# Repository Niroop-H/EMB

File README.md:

# EMB native KiCad automation

See [desktop automation setup, verification policy and Windows packaging](kicad_ai/AUTOMATION.md).
The automation companion preserves the original KiCad editors and engines.
Legacy generated certificates are not manufacturing approvals.

# KiCad README

For specific documentation about [building KiCad](https://dev-docs.kicad.org/en/build/), policies
and guidelines, and source code documentation see the
[Developer Documentation](https://dev-docs.kicad.org) website.

You may also take a look into the [Wiki](https://gitlab.com/kicad/code/kicad/-/wikis/home),
the [contribution guide](https://dev-docs.kicad.org/en/contribute/).

For general information about KiCad and information about contributing to the documentation and
libraries, see our [Website](https://kicad.org/) and our [Forum](https://forum.kicad.info/).

## Build state

KiCad uses a host of CI resources.

GitLab CI pipeline status can be viewed for Linux and Windows builds of the latest commits.

## Release status

## Files
* [AUTHORS.txt](AUTHORS.txt) - The authors, contributors, document writers and translators list
* [CMakeLists.txt](CMakeLists.txt) - Main CMAKE build tool script
* [copyright.h](copyright.h) - A very short copy of the GNU General Public License to be included in new source files
* [Doxyfile](Doxyfile) - Doxygen config file for KiCad
* [INSTALL.txt](INSTALL.txt) - The release (binary) installation instructions
* [uncrustify.cfg](uncrustify.cfg) - Uncrustify config file for uncrustify sources formatting tool
* [_clang-format](_clang-format) - clang config file for clang-format sources formatting tool

## Subdirectories

* [3d-viewer](3d-viewer)         - Sourcecode of the 3D viewer
* [cmake](cmake)      - Modules for the CMAKE build tool
* [common](common)            - Sourcecode of the common library
* [cvpcb](cvpcb)             - Sourcecode of the CvPCB tool
* [demos](demos)             - Some demo examples
* [doxygen](doxygen)     - Configuration for generating pretty doxygen manual of the codebase
* [eeschema](eeschema)          - Sourcecode of the schematic editor
* [gerbview](gerbview)          - Sourcecode of the gerber viewer
* [include](include)           - Interfaces to the common library
* [kicad](kicad)             - Sourcecode of the project manager
* [libs](libs)           - Sourcecode of KiCad utilities (geometry and others)
* [pagelayout_editor](pagelayout_editor) - Sourcecode of the pagelayout editor
* [patches](patches)           - Collection of patches for external dependencies
* [pcbnew](pcbnew)           - Sourcecode of the printed circuit board editor
* [plugins](plugins)           - Sourcecode for the 3D viewer plugins
* [qa](qa)                - Unit testing framework for KiCad
* [resources](resources)         - Packaging resources such as bitmaps and operating system specific files
    - [bitmaps_png](resources/bitmaps_png)       - Menu and program icons
    - [project_template](resources/project_template)          - Project template
* [thirdparty](thirdparty)           - Sourcecode of external libraries used in KiCad but not written by the KiCad team
* [tools](tools)             - Helpers for developing, testing and building
* [translation](translation) - Translation data files (managed through [Weblate](https://hosted.weblate.org/projects/kicad/master-source/) for most languages)
* [utils](utils)             - Small utils for KiCad, e.g. IDF, STEP, and OGL tools and converters

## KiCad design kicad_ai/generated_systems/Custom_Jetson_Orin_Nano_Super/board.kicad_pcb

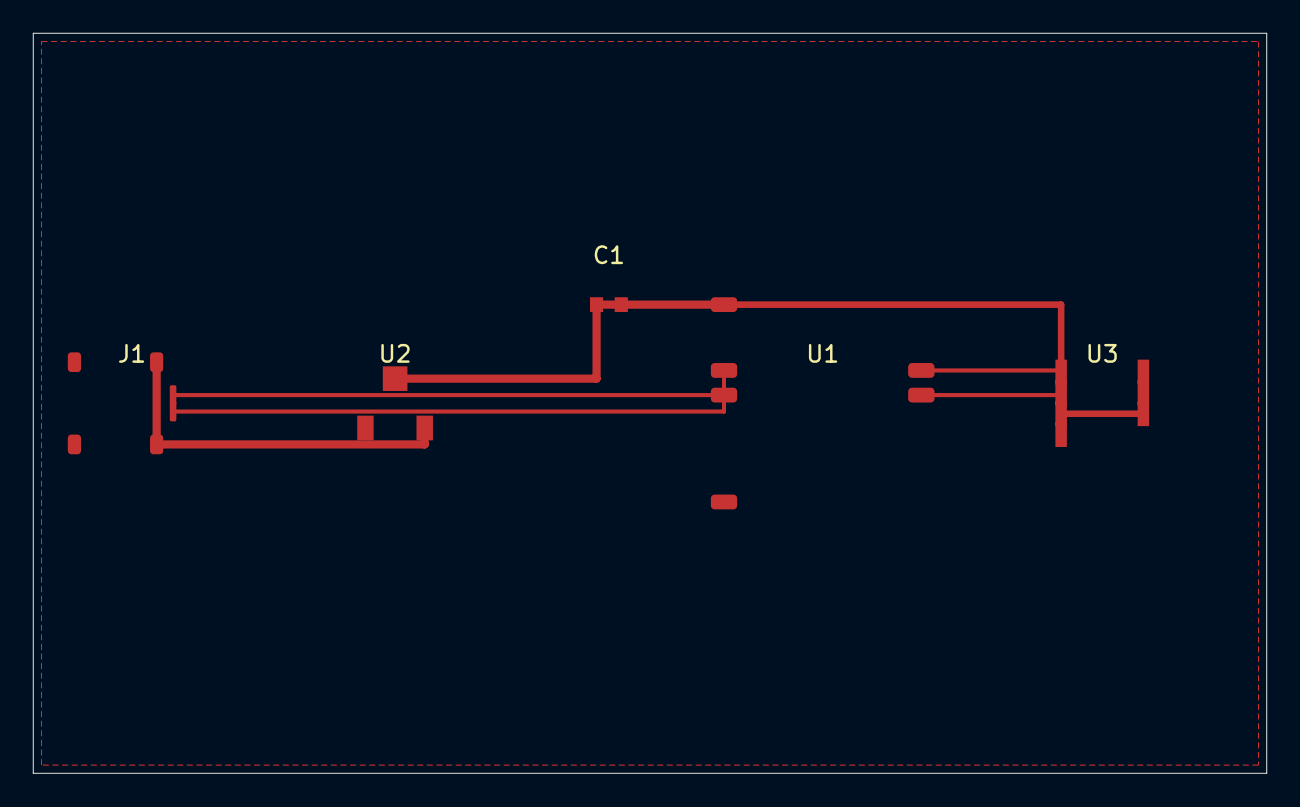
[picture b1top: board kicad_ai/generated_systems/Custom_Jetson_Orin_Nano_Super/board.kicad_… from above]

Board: 2 copper layers, 75.0 x 45.0 mm, 5 parts (0 on the bottom side), 7 nets.

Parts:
C1: 100nF; C_0603_1608Metric
J1: USB-C; USB_C_Receptacle_HRO_TYPE-C-31-M-12
U1: ESP32-S3; ESP32-S3-WROOM-1
U2: AMS1117-3.3; SOT-223-3_TabPin2
U3: SN65HVD230DR; SOIC-8_3.9x4.9mm_P1.27mm

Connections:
+3V3: C1.1, U1.2, U2.2, U3.3, U3.8
CAN_RX: U1.5, U3.4
CAN_TX: U1.4, U3.1
GND: C1.2, J1.A1, J1.B1, U1.1, U2.1, U3.2
USB_DN: J1.A7, U1.20
USB_DP: J1.A6, U1.19
VBUS: J1.A4, J1.B4, U2.3

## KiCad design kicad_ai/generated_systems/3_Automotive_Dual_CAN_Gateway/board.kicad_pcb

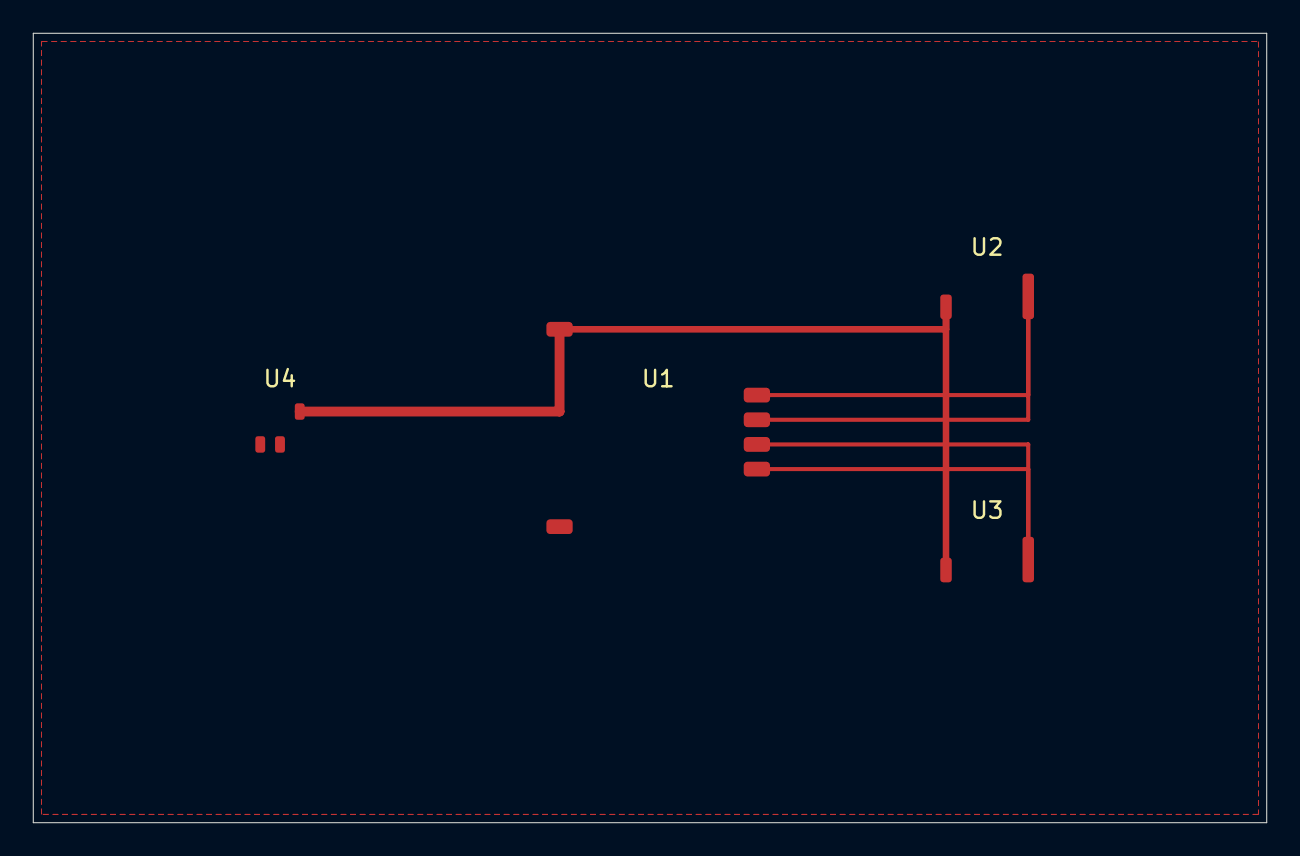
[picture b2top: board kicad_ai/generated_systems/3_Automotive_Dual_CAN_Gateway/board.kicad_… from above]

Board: 2 copper layers, 75.0 x 48.0 mm, 4 parts (0 on the bottom side), 6 nets.

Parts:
U1: ESP32-S3; ESP32-S3-WROOM-1
U2: CAN1; SOIC-8_3.9x4.9mm_P1.27mm
U3: CAN2; SOIC-8_3.9x4.9mm_P1.27mm
U4: TPS54302; SOT-23-6

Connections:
+3V3: U1.2, U2.3, U3.3, U4.6
CAN1_H: U1.4, U2.7
CAN1_L: U1.5, U2.6
CAN2_H: U1.6, U3.7
CAN2_L: U1.7, U3.6
GND: U1.1, U4.2

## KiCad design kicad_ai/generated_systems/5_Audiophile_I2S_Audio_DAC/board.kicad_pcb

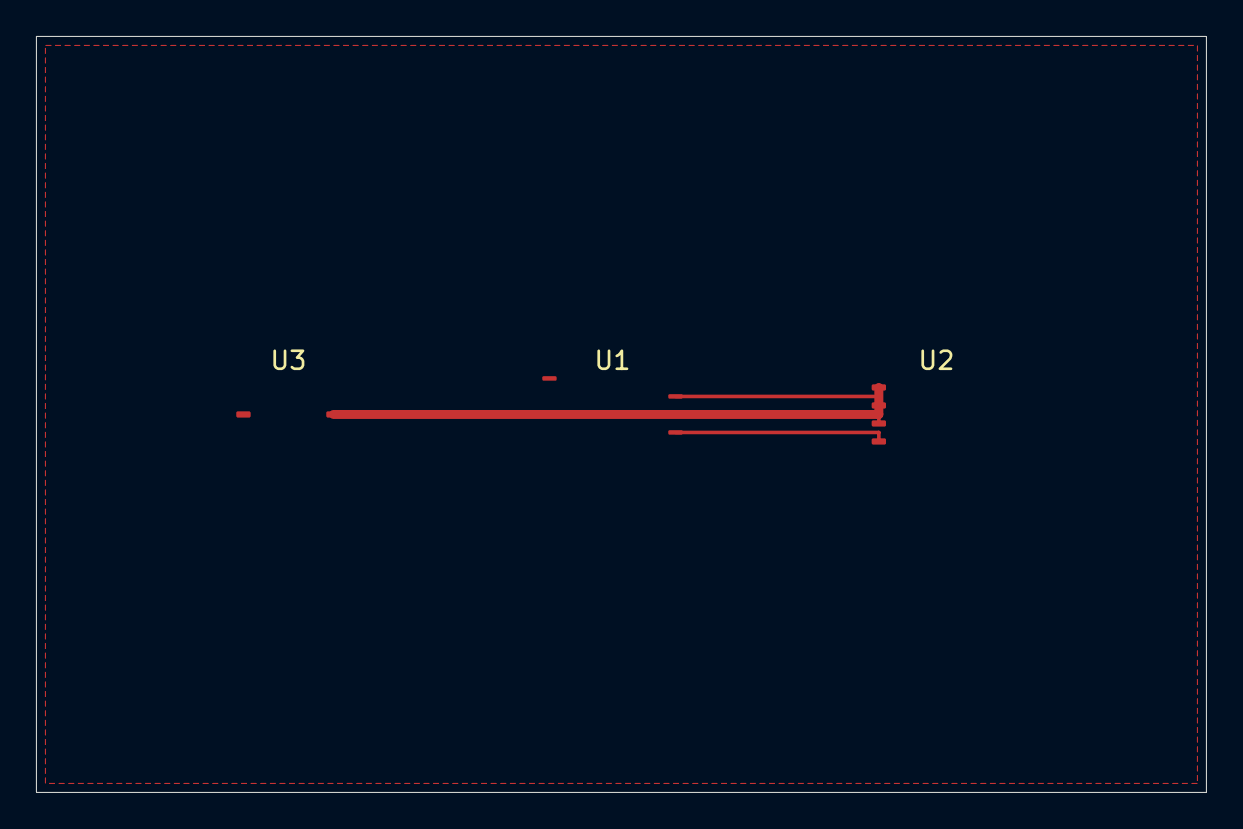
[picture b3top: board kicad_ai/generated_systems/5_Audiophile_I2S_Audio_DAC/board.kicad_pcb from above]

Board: 2 copper layers, 65.0 x 42.0 mm, 3 parts (0 on the bottom side), 4 nets.

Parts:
U1: RP2040; QFN-56-1EP_7x7mm_P0.4mm_EP3.2x3.2mm
U2: PCM5102A; TSSOP-20_4.4x6.5mm_P0.65mm
U3: TPS7A47; QFN-20-1EP_5x5mm_P0.65mm_EP3.1x3.1mm

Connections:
+3V3_ANA: U2.1, U3.5
I2S_BCLK: U1.15, U2.12
I2S_DATA: U1.17, U2.14
I2S_LRCK: U1.16, U2.13

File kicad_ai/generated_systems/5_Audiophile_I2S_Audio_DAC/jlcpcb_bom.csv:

Comment,Designator,Footprint,LCSC Part #
RP2040,U1,Package_DFN_QFN:QFN-56-1EP_7x7mm_P0.4mm_EP3.2x3.2mm,TBD
PCM5102APWR,U2,Package_SO:TSSOP-20_4.4x6.5mm_P0.65mm,TBD
TPS7A4700RGWR,U3,Package_DFN_QFN:QFN-20-1EP_5x5mm_P0.65mm_EP3.1x3.1mm,TBD

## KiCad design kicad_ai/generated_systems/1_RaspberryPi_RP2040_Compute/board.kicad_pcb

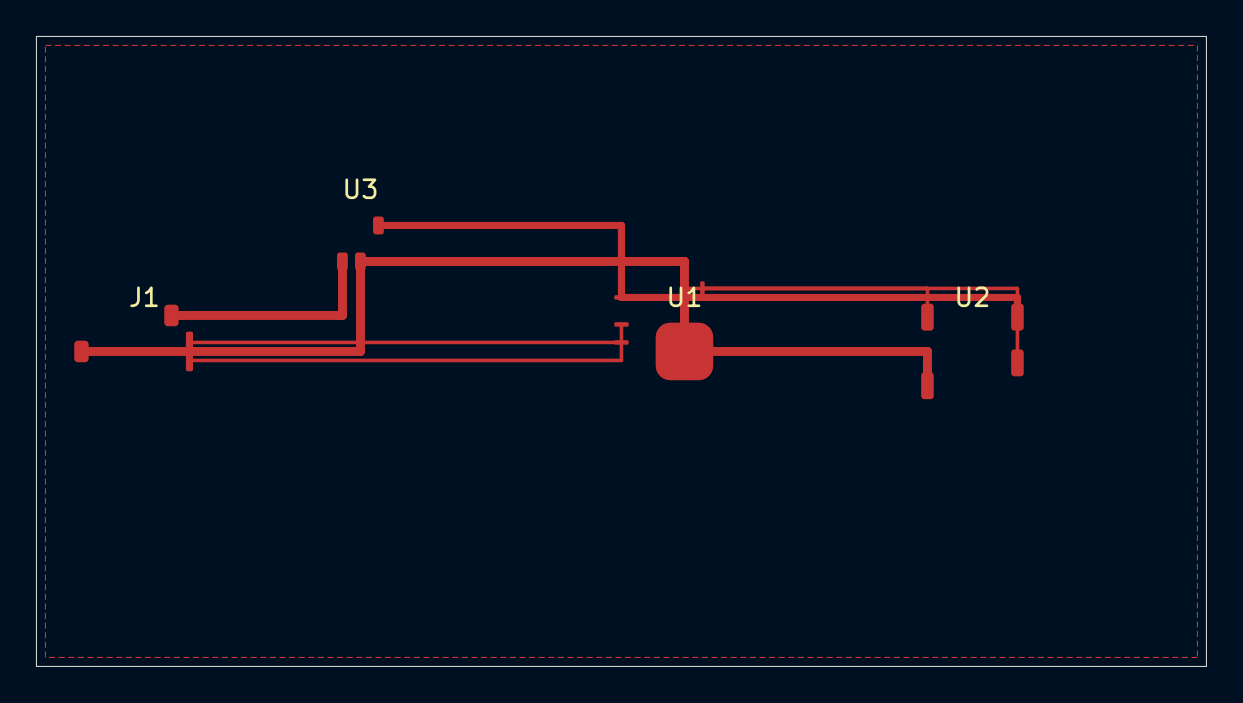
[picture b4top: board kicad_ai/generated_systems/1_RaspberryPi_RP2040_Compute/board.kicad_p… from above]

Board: 2 copper layers, 65.0 x 35.0 mm, 4 parts (0 on the bottom side), 7 nets.

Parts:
J1: USB-C; USB_C_Receptacle_HRO_TYPE-C-31-M-12
U1: RP2040; QFN-56-1EP_7x7mm_P0.4mm_EP3.2x3.2mm
U2: W25Q128; SOIC-8_5.23x5.23mm_P1.27mm
U3: NCP115; SOT-23-5

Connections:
+3V3: U1.1, U2.8, U3.5
GND: J1.A1, U1.57, U2.4, U3.2
QSPI_CLK: U1.52, U2.6
QSPI_CS: U1.53, U2.1
USB_DN: J1.A7, U1.3
USB_DP: J1.A6, U1.2
VBUS: J1.A4, U3.1

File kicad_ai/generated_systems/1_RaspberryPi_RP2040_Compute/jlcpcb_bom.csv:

Comment,Designator,Footprint,LCSC Part #
RP2040,U1,Package_DFN_QFN:QFN-56-1EP_7x7mm_P0.4mm_EP3.2x3.2mm,TBD
W25Q128JVS,U2,Package_SO:SOIC-8_5.23x5.23mm_P1.27mm,TBD
NCP115AMX330TCG,U3,Package_TO_SOT_SMD:SOT-23-5,TBD
TYPE-C-31-M-12,J1,Connector_USB:USB_C_Receptacle_HRO_TYPE-C-31-M-12,TBD
ABLS-12.000MHZ-B4-T,Y1,Crystal:Crystal_SMD_HC49-SD,TBD

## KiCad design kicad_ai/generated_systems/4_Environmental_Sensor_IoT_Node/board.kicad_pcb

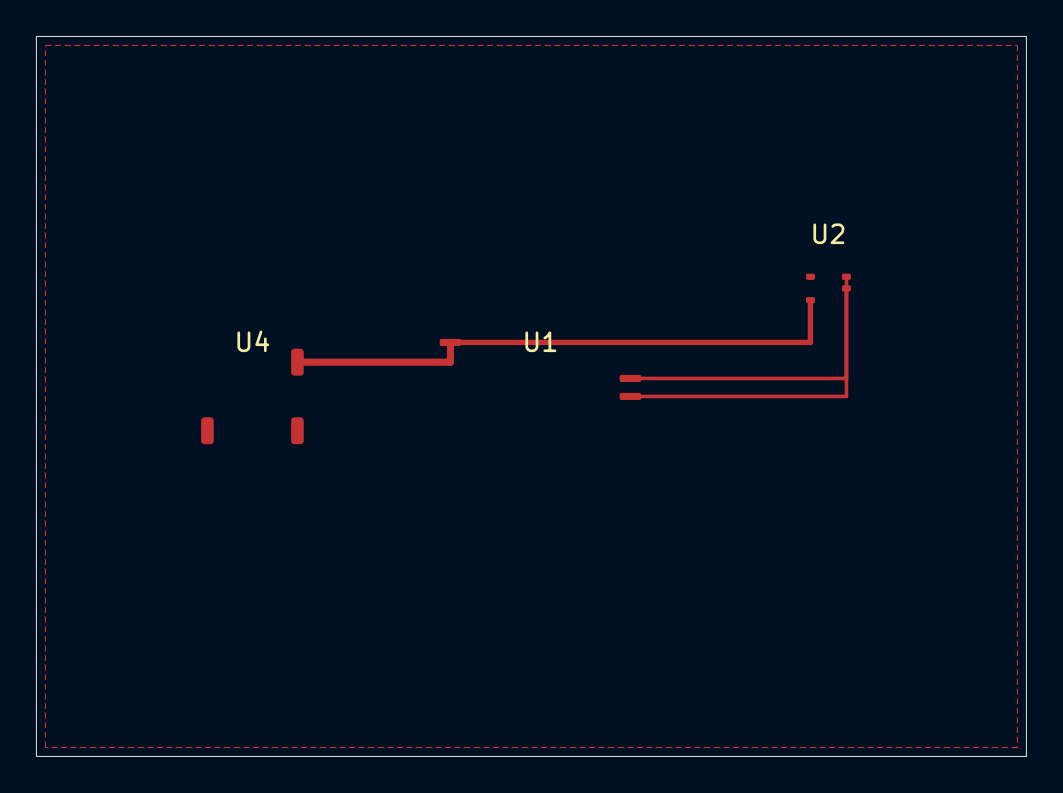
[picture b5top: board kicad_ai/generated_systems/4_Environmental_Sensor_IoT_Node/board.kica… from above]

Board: 2 copper layers, 55.0 x 40.0 mm, 3 parts (0 on the bottom side), 4 nets.

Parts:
U1: ESP32-C3; ESP32-C3-MINI-1
U2: BME280; LGA-8_2.5x2.5mm_P0.65mm_Clockwise
U4: TP4056; SOIC-8_3.9x4.9mm_P1.27mm

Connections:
+3V3: U1.1, U2.8, U4.8
GND: U2.1, U4.4
I2C_SCL: U1.5, U2.4
I2C_SDA: U1.4, U2.3

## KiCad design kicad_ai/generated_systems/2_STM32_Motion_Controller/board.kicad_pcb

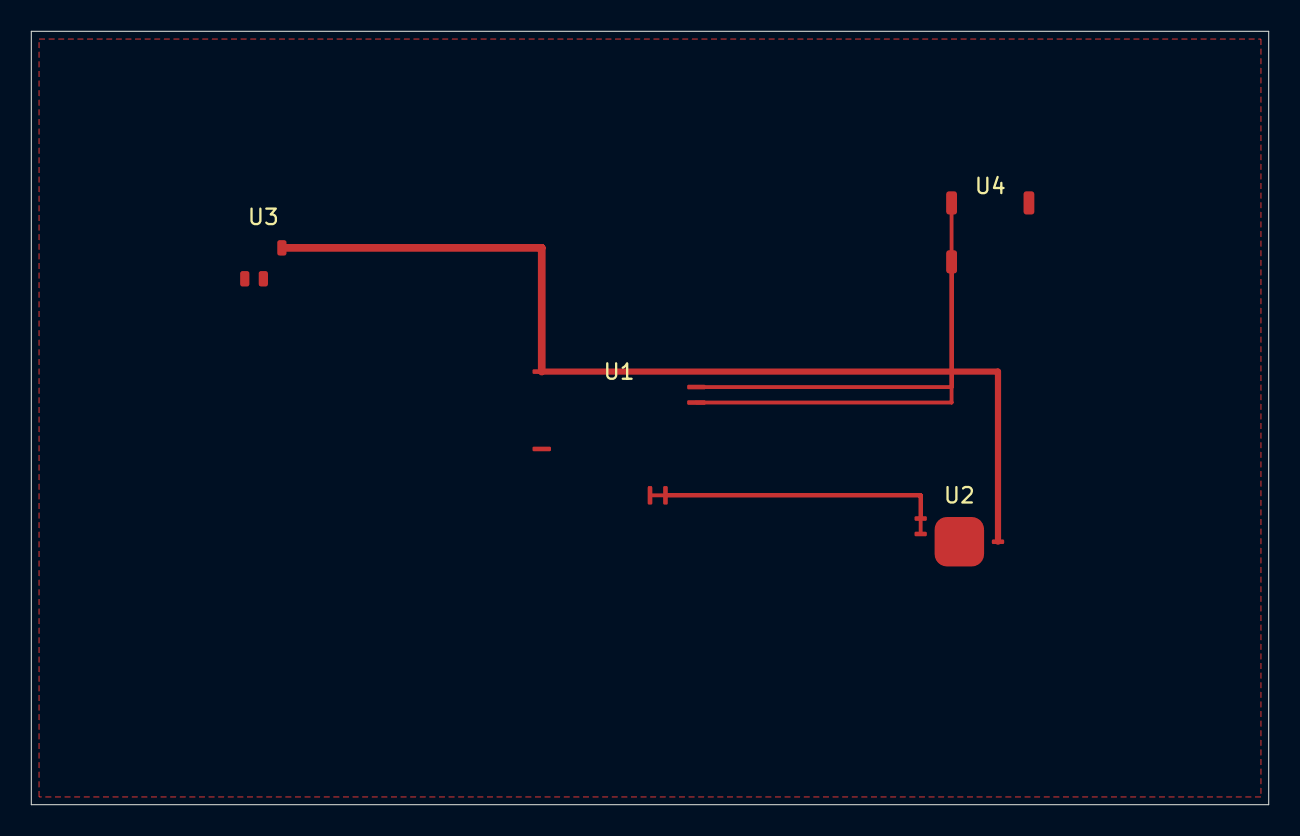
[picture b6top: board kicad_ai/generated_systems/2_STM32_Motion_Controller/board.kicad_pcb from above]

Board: 2 copper layers, 80.0 x 50.0 mm, 4 parts (0 on the bottom side), 6 nets.

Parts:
U1: STM32F405; LQFP-64_10x10mm_P0.5mm
U2: TMC2209; QFN-28-1EP_5x5mm_P0.5mm_EP3.25x3.25mm
U3: TPS54302; SOT-23-6
U4: MAX485; SOIC-8_3.9x4.9mm_P1.27mm

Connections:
+3V3: U1.1, U2.15, U3.6, U4.8
DIR_X: U1.21, U2.2
GND: U1.12, U2.29, U3.2
RS485_A: U1.35, U4.1
RS485_B: U1.36, U4.4
STEP_X: U1.20, U2.1

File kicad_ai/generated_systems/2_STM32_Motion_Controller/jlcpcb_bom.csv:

Comment,Designator,Footprint,LCSC Part #
STM32F405RGT6,U1,Package_QFP:LQFP-64_10x10mm_P0.5mm,TBD
TMC2209-LA,U2,Package_DFN_QFN:QFN-28-1EP_5x5mm_P0.5mm_EP3.25x3.25mm,TBD
TPS54302DDCR,U3,Package_TO_SOT_SMD:SOT-23-6,TBD
MAX485ESA+,U4,Package_SO:SOIC-8_3.9x4.9mm_P1.27mm,TBD

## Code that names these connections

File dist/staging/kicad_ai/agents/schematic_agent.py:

"""
Schematic Synthesis Agent.
Converts system architecture -> complete, ERC-ready .kicad_sch
"""

from typing import Dict, Any
from .base_agent import BaseHardwareAgent
from ..sexpr.sch_builder import SchematicBuilder


class SchematicAgent(BaseHardwareAgent):
    def __init__(self):
        super().__init__(
            name="SchematicSynthesizer",
            role_description="KiCad Schematic Synthesizer"
        )
        self.set_system_prompt(
            "You are an expert KiCad schematic designer. "
            "Lay out symbols cleanly, wire all nets, "
            "add decoupling caps, pull-ups, and PWR_FLAG symbols to pass ERC."
        )

    def synthesize_schematic(self, architecture: Dict[str, Any], output_path: str) -> str:
        builder = SchematicBuilder(title=architecture.get("project_name", "Embedded System"))
        mcu = architecture.get("mcu", {})
        components = architecture.get("components", [])

        # ── Grid origin ───────────────────────────────────────────
        ox, oy = 80.0, 70.0

        # ── U1 MCU ───────────────────────────────────────────────
        u1x, u1y = ox + 100.0, oy + 40.0
        builder.add_symbol(
            lib_id=mcu.get("lib_id", "RF_Module:ESP32-S3-WROOM-1"),
            reference=mcu.get("reference", "U1"),
            value=mcu.get("mpn", "ESP32-S3"),
            footprint=mcu.get("footprint", ""),
            x=u1x, y=u1y
        )

        # MCU decoupling: 100nF x2, 10uF x1
        cap_idx = 1
        for cap_val, cap_fp in [("100nF", "Capacitor_SMD:C_0603_1608Metric"),
                                 ("100nF", "Capacitor_SMD:C_0603_1608Metric"),
                                 ("10uF",  "Capacitor_SMD:C_0805_2012Metric")]:
            cx, cy = u1x - 35.0, u1y - 20.0 + cap_idx * 12.0
            builder.add_symbol("Device:C_Small", f"C{cap_idx}", cap_val, cap_fp, cx, cy)
            builder.add_wire(cx, cy - 6.0, cx, cy - 4.0)
            builder.add_net_label("+3V3", cx, cy - 6.0)
            builder.add_wire(cx, cy + 4.0, cx, cy + 6.0)
            builder.add_power_symbol("GND", cx, cy + 10.0)
            cap_idx += 1

        # EN pull-up resistor
        builder.add_symbol("Device:R_Small", "R1", "10k",
                            "Resistor_SMD:R_0603_1608Metric",
                            u1x - 25.0, u1y - 25.0)
        builder.add_net_label("+3V3", u1x - 25.0, u1y - 31.0)
        builder.add_net_label("ESP_EN", u1x - 25.0, u1y - 20.0)

        res_idx = 2  # R1 used above

        # ── U2 Regulator ─────────────────────────────────────────
        for comp in components:
            ref = comp.get("reference", "")
            if ref in ("U1", ""):
                continue

            if ref == "U2":
                u2x, u2y = ox + 20.0, u1y
                builder.add_symbol(
                    comp.get("lib_id", "Regulator_Linear:AMS1117-3.3"),
                    ref, comp.get("mpn", "AMS1117-3.3"),
                    comp.get("footprint", ""),
                    u2x, u2y
                )
                builder.add_net_label("VBUS", u2x - 15.0, u2y)
                builder.add_wire(u2x - 15.0, u2y, u2x, u2y)
                builder.add_net_label("+3V3", u2x + 15.0, u2y)
                builder.add_wire(u2x, u2y, u2x + 15.0, u2y)
                builder.add_power_symbol("GND", u2x, u2y + 12.0)
                # Output filter cap
                builder.add_symbol("Device:C_Small", f"C{cap_idx}", "10uF",
                                   "Capacitor_SMD:C_0805_2012Metric",
                                   u2x + 25.0, u2y + 5.0)
                builder.add_net_label("+3V3", u2x + 25.0, u2y - 1.0)
                builder.add_power_symbol("GND", u2x + 25.0, u2y + 15.0)
                cap_idx += 1

            elif ref == "J1":
                # USB-C connector
                j1x, j1y = ox + 20.0, u1y + 65.0
                builder.add_symbol(
                    comp.get("lib_id", "Connector:USB_C_Receptacle_USB2.0_16P"),
                    ref, comp.get("mpn", "TYPE-C-31-M-12"),
                    comp.get("footprint", ""),
                    j1x, j1y
                )
                builder.add_net_label("VBUS", j1x + 20.0, j1y - 20.0)
                builder.add_net_label("USB_DP", j1x + 20.0, j1y - 10.0)
                builder.add_net_label("USB_DN", j1x + 20.0, j1y)
                builder.add_power_symbol("GND", j1x, j1y + 25.0)

                # CC1 / CC2 5.1kΩ pull-downs (required by USB-C spec)
                for cc_i in range(2):
                    rcc_x = j1x - 20.0
                    rcc_y = j1y + 30.0 + cc_i * 15.0
                    r_ref = f"R{res_idx}"
                    res_idx += 1
                    builder.add_symbol("Device:R_Small", r_ref, "5.1k",
                                       "Resistor_SMD:R_0603_1608Metric",
                                       rcc_x, rcc_y)
                    builder.add_net_label(f"CC{cc_i+1}", rcc_x, rcc_y - 6.0)
                    builder.add_power_symbol("GND", rcc_x, rcc_y + 10.0)

                # MCU USB net connections
                builder.add_net_label("USB_DP", u1x - 20.0, u1y + 20.0)
                builder.add_net_label("USB_DN", u1x - 20.0, u1y + 30.0)

            elif ref == "U3":
                # CAN Transceiver
                u3x, u3y = u1x + 80.0, u1y
                builder.add_symbol(
                    comp.get("lib_id", "Interface_CAN_LIN:SN65HVD230"),
                    ref, comp.get("mpn", "SN65HVD230DR"),
                    comp.get("footprint", ""),
                    u3x, u3y
                )
                builder.add_net_label("CAN_TX", u3x - 20.0, u3y - 10.0)
                builder.add_net_label("CAN_RX", u3x - 20.0, u3y)
                builder.add_net_label("+3V3", u3x, u3y - 15.0)
                builder.add_power_symbol("GND", u3x, u3y + 15.0)
                builder.add_net_label("CAN_TX", u1x + 20.0, u1y - 10.0)
                builder.add_net_label("CAN_RX", u1x + 20.0, u1y)

                # 120Ω CAN bus termination
                r_term = f"R{res_idx}"
                res_idx += 1
                builder.add_symbol("Device:R_Small", r_term, "120R",
                                   "Resistor_SMD:R_0603_1608Metric",
                                   u3x + 30.0, u3y - 5.0)
                builder.add_net_label("CAN_H", u3x + 30.0, u3y - 11.0)
                builder.add_net_label("CAN_L", u3x + 30.0, u3y + 1.0)
                builder.add_net_label("CAN_H", u3x + 20.0, u3y - 10.0)
                builder.add_net_label("CAN_L", u3x + 20.0, u3y + 5.0)

        # ── PWR_FLAGs (required to suppress ERC "power pin not driven") ──
        for pnet, px, py in [("+3V3", ox, oy), ("GND", ox, oy + 15.0), ("VBUS", ox, oy + 30.0)]:
            builder.add_pwr_flag(px, py)
            builder.add_net_label(pnet, px + 10.0, py)

        builder.save(output_path)
        return output_path
